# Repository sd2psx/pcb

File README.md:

# sd2psx: PCB

<table>
<tr>
    <td></td>
    <td></td>
    <td></td>
</tr>
</table>

## Production notes

The PCB must be produced in 0.8mm thickness. Production files are provided under the "Releases" tab. These do not include the through-hole OLED module.

## PSRAM notes (LY68L6400SLIT)

As of June 2023, the LY68L6400SLIT is no longer available from JLCPCB. I've also seen multiple reports of people receiving a **fake chip** when purchasing one from aliexpress. The following chips are a drop-in replacement for the PSRAM:

* IPUS IPS6404LSQ
* ESP PSRAM64H
* AP 6404L-3SQR - Available from [Mouser](https://www.mouser.com/ProductDetail/AP-Memory/APS6404L-3SQR-SN?qs=IS%252B4QmGtzzqsn3S5xo%2FEEg%3D%3D)
* Lyontek LY68L6400S

I recommend switching to the AP 6404L-3SQR module; it can be assembled by JLCPCB by first ordering it into your [personal parts library](https://jlcpcb.com/user-center/smtPrivateLibrary/?index=1).

## OLED module notes

The case requires a slim OLED module. The more common full-sized module will not fit into the case:

Examples of compatible modules:
- https://detail.tmall.com/item.htm?id=534583545403&skuId=3942158349315
- https://www.aliexpress.com/item/32638662748.html (make sure to select the smaller module marked as "New-White")

Spec sheet of a compatible module:

**Make sure that the pinout goes GND/VCC/SCL/SDA**. There are modules that swap GND/VCC around, these won't work.

## Assembly tips

When attaching the module to the PCB, remove protective OLED screen film (to prevent misalignment), then drop the module into the case so that the screen ends up flush against the case wall. Solder it on in that setup, then clip the pins:

There may be extra space between the pin header and the PCB, depending on your 3d print tolerances, but when fully assembled it should look nice and flush.

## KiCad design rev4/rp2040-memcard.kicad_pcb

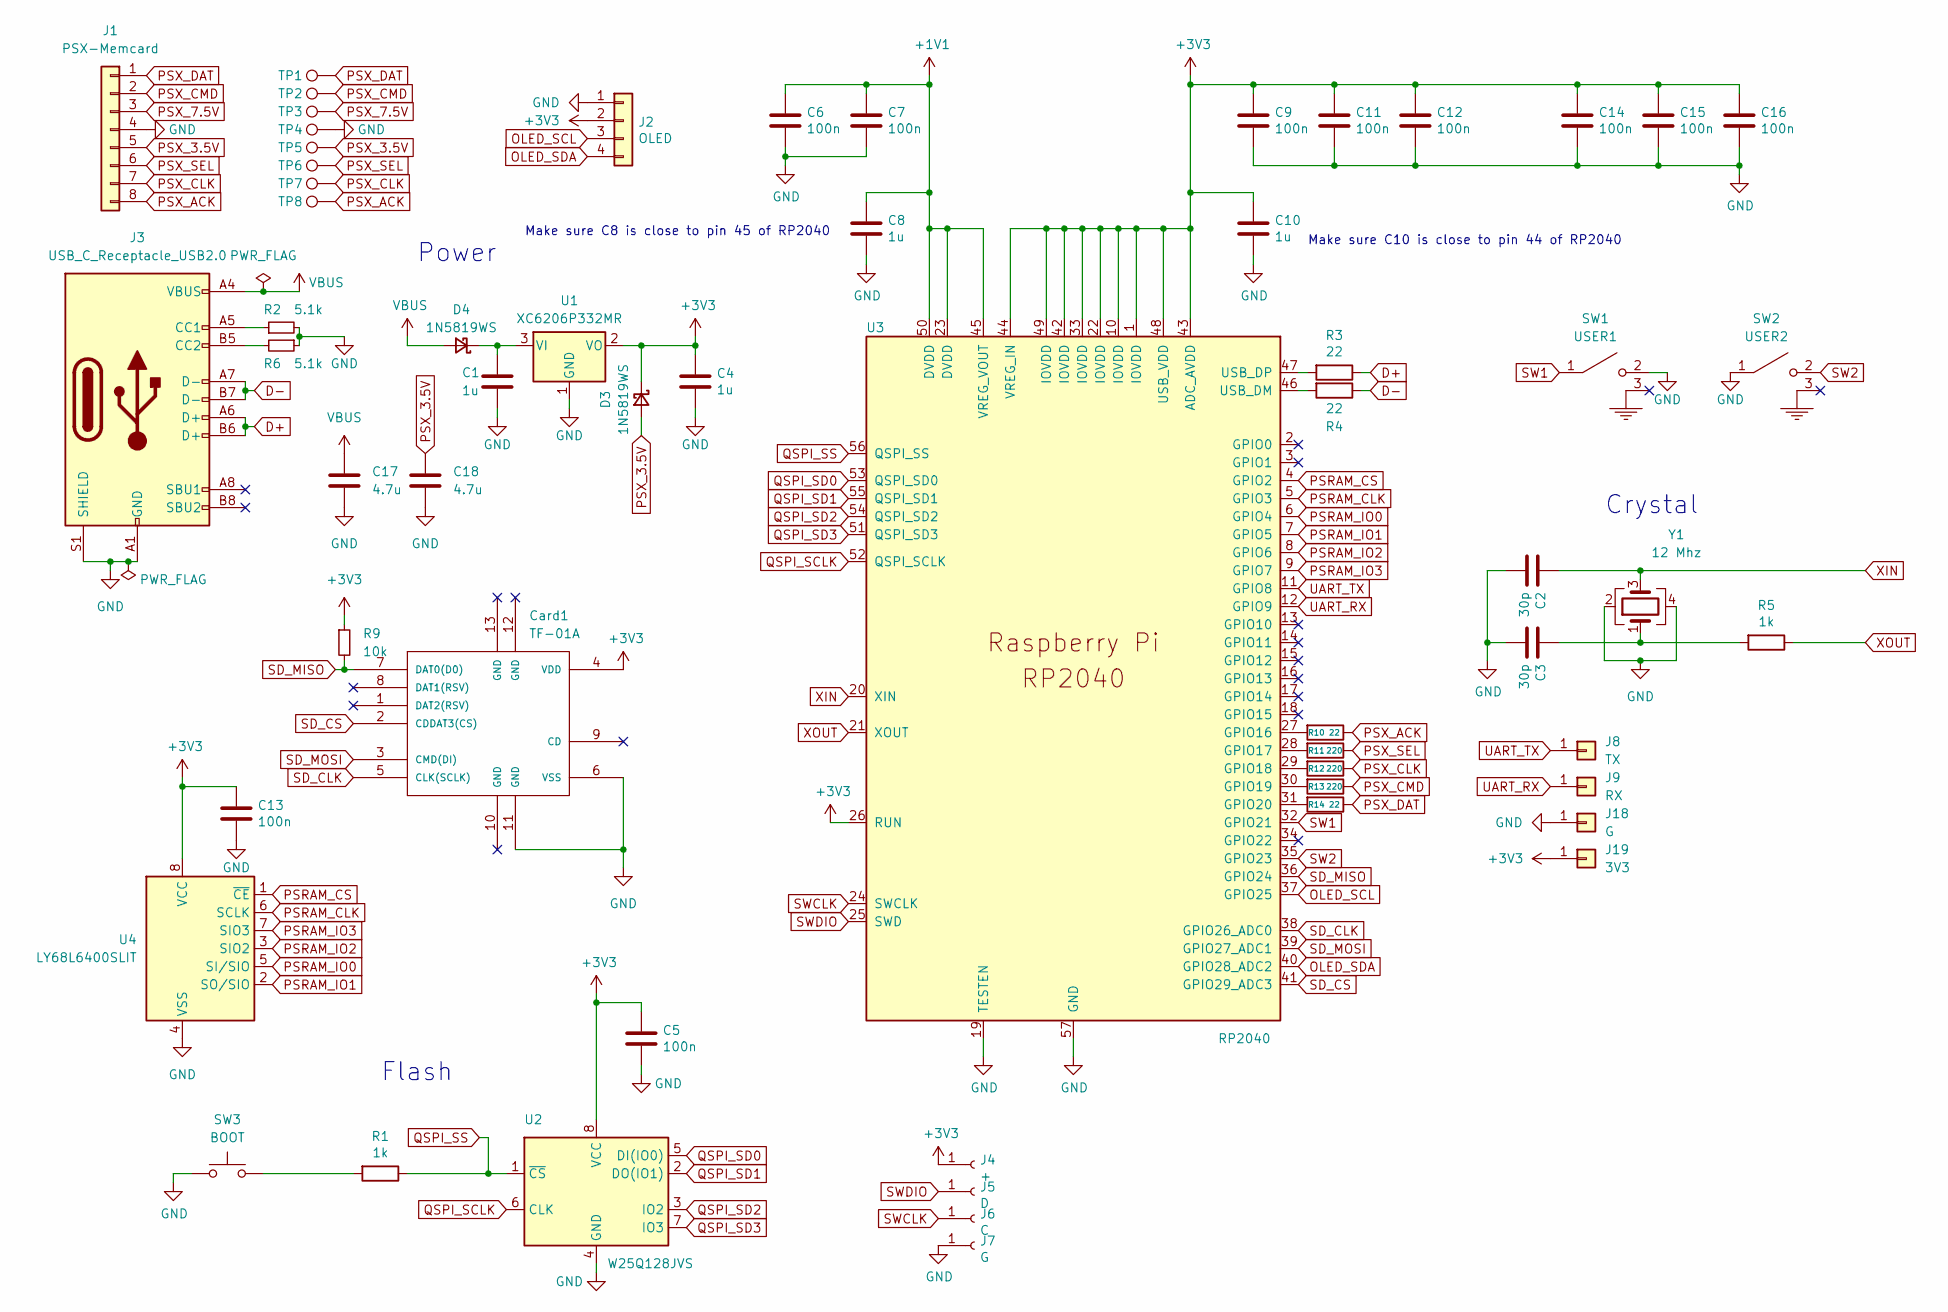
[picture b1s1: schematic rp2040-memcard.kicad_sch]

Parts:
C1, C4, C8, C10: 1u; C_0402_1005Metric; LCSC C52923
C2, C3: 30p; C_0402_1005Metric; LCSC C1570
C5, C6, C7, C9, C11, C12, C13, C14, C15, C16: 100n; C_0402_1005Metric; LCSC C1525
C17, C18: 4.7u; C_0402_1005Metric; LCSC C23733
Card1: TF-01A; TF-SMD_TF-01A; LCSC C91145
D3, D4: 1N5819WS; D_SOD-323; LCSC C191023
J1: PSX-Memcard; PlayStation_Memory_Card
J2: OLED; SSD1306
J3: USB_C_Receptacle_USB2.0; USB_C_Receptacle_HRO_TYPE-C-31-M-12; LCSC C2765186
J4: +; TestPoint_Pad_D1.5mm
J5: D; TestPoint_Pad_D1.5mm
J6: C; TestPoint_Pad_D1.5mm
J7: G; TestPoint_Pad_D1.5mm
J8: TX; TestPoint_Pad_D1.0mm
J9: RX; TestPoint_Pad_D1.0mm
J18: G; TestPoint_Pad_D1.0mm
J19: 3V3; TestPoint_Pad_D1.0mm
R1, R5: 1k; R_0402_1005Metric; LCSC C11702
R2, R6: 5.1k; R_0402_1005Metric; LCSC C25905
R3, R4, R10, R14: 22; R_0402_1005Metric; LCSC C25092
R9: 10k; R_0402_1005Metric; LCSC C25744
R11, R12, R13: 220; R_0402_1005Metric; LCSC C25091
SW1: USER1; SW-TH_TSC017A10026A
SW2: USER2; SW-TH_TSC017A10026A
SW3: BOOT; PinHeader_1x02_P2.00mm_Vertical; LCSC C393942
TP1, TP2, TP3, TP4, TP5, TP6, TP7, TP8: TestPoint; TestPoint_Pad_D1.0mm
U1: XC6206P332MR; SOT-23; LCSC C5446
U2: W25Q128JVS; SOIC-8_5.23x5.23mm_P1.27mm; LCSC C97521
U3: RP2040; RP2040-QFN-56; LCSC C2040
U4: LY68L6400SLIT; SOIC-8_3.9x4.9mm_P1.27mm; LCSC C261881
Y1: 12 Mhz; Crystal_SMD_3225-4Pin_3.2x2.5mm; LCSC C9002

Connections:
+1V1: C6.1, C7.1, C8.1, U3.23 (DVDD), U3.45 (VREG_VOUT), U3.50 (DVDD)
+3V3: C4.1, C5.1, C9.1, C10.1, C11.1, C12.1, C13.1, C14.1, C15.1, C16.1, Card1.4 (VDD), D3.1 (K), J2.2, J4.1, J19.1, R9.1, U1.2 (VO), U2.8 (VCC), U3.1 (IOVDD), U3.10 (IOVDD), U3.22 (IOVDD), U3.26 (RUN), U3.33 (IOVDD), U3.42 (IOVDD), U3.43 (ADC_AVDD), U3.44 (VREG_IN), U3.48 (USB_VDD), U3.49 (IOVDD), U4.8 (VCC)
D+: J3.A6 (D+), J3.B6 (D+), R3.1
D-: J3.A7 (D-), J3.B7 (D-), R4.1
GND: C1.2, C2.2, C3.2, C4.2, C5.2, C6.2, C7.2, C8.2, C9.2, C10.2, C11.2, C12.2, C13.2, C14.2, C15.2, C16.2, C17.1, C18.1, Card1.6 (VSS), Card1.11 (GND), J1.4, J2.1, J3.A1 (GND), J3.A12 (GND), J3.B1 (GND), J3.B12 (GND), J3.S1 (SHIELD), J7.1, J18.1, R2.2, R6.1, SW1.2, SW2.1, SW3.1, TP4.1, U1.1 (GND), U2.4 (GND), U3.19 (TESTEN), U3.57 (GND), U4.4 (VSS), Y1.2, Y1.4
unnamed: C1.1, D4.1 (K), U1.3 (VI)
unnamed: C3.1, R5.2, Y1.1
unnamed: J3.A5 (CC1), R2.1
unnamed: J3.B5 (CC2), R6.2
unnamed: R1.2, SW3.2
unnamed: R3.2, U3.47 (USB_DP)
unnamed: R4.2, U3.46 (USB_DM)
unnamed: R10.2, U3.27 (GPIO16)
unnamed: R11.2, U3.28 (GPIO17)
unnamed: R12.2, U3.29 (GPIO18)
unnamed: R13.2, U3.30 (GPIO19)
unnamed: R14.2, U3.31 (GPIO20)
OLED_SCL: J2.3, U3.37 (GPIO25)
OLED_SDA: J2.4, U3.40 (GPIO28_ADC2)
PSRAM_CLK: U3.5 (GPIO3), U4.6 (SCLK)
PSRAM_CS: U3.4 (GPIO2), U4.1 (~CE)
PSRAM_IO0: U3.6 (GPIO4), U4.5 (SI/SIO)
PSRAM_IO1: U3.7 (GPIO5), U4.2 (SO/SIO)
PSRAM_IO2: U3.8 (GPIO6), U4.3 (SIO2)
PSRAM_IO3: U3.9 (GPIO7), U4.7 (SIO3)
PSX_3.5V: C18.2, D3.2 (A), J1.5, TP5.1
PSX_7.5V: J1.3, TP3.1
PSX_ACK: J1.8, R10.1, TP8.1
PSX_CLK: J1.7, R12.1, TP7.1
PSX_CMD: J1.2, R13.1, TP2.1
PSX_DAT: J1.1, R14.1, TP1.1
PSX_SEL: J1.6, R11.1, TP6.1
QSPI_SCLK: U2.6 (CLK), U3.52 (QSPI_SCLK)
QSPI_SD0: U2.5 (DI(IO0)), U3.53 (QSPI_SD0)
QSPI_SD1: U2.2 (DO(IO1)), U3.55 (QSPI_SD1)
QSPI_SD2: U2.3 (IO2), U3.54 (QSPI_SD2)
QSPI_SD3: U2.7 (IO3), U3.51 (QSPI_SD3)
QSPI_SS: R1.1, U2.1 (~CS), U3.56 (QSPI_SS)
SD_CLK: Card1.5 (CLK(SCLK)), U3.38 (GPIO26_ADC0)
SD_CS: Card1.2 (CDDAT3(CS)), U3.41 (GPIO29_ADC3)
SD_MISO: Card1.7 (DAT0(D0)), R9.2, U3.36 (GPIO24)
SD_MOSI: Card1.3 (CMD(DI)), U3.39 (GPIO27_ADC1)
SW1: SW1.1, U3.32 (GPIO21)
SW2: SW2.2, U3.35 (GPIO23)
SWCLK: J6.1, U3.24 (SWCLK)
SWDIO: J5.1, U3.25 (SWD)
UART_RX: J9.1, U3.12 (GPIO9)
UART_TX: J8.1, U3.11 (GPIO8)
VBUS: C17.2, D4.2 (A), J3.A4 (VBUS), J3.A9 (VBUS), J3.B4 (VBUS), J3.B9 (VBUS)
XIN: C2.1, U3.20 (XIN), Y1.3
XOUT: R5.1, U3.21 (XOUT)

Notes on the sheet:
Make sure C10 is close to pin 44 of RP2040
Make sure C8 is close to pin 45 of RP2040
Crystal
Power
Flash

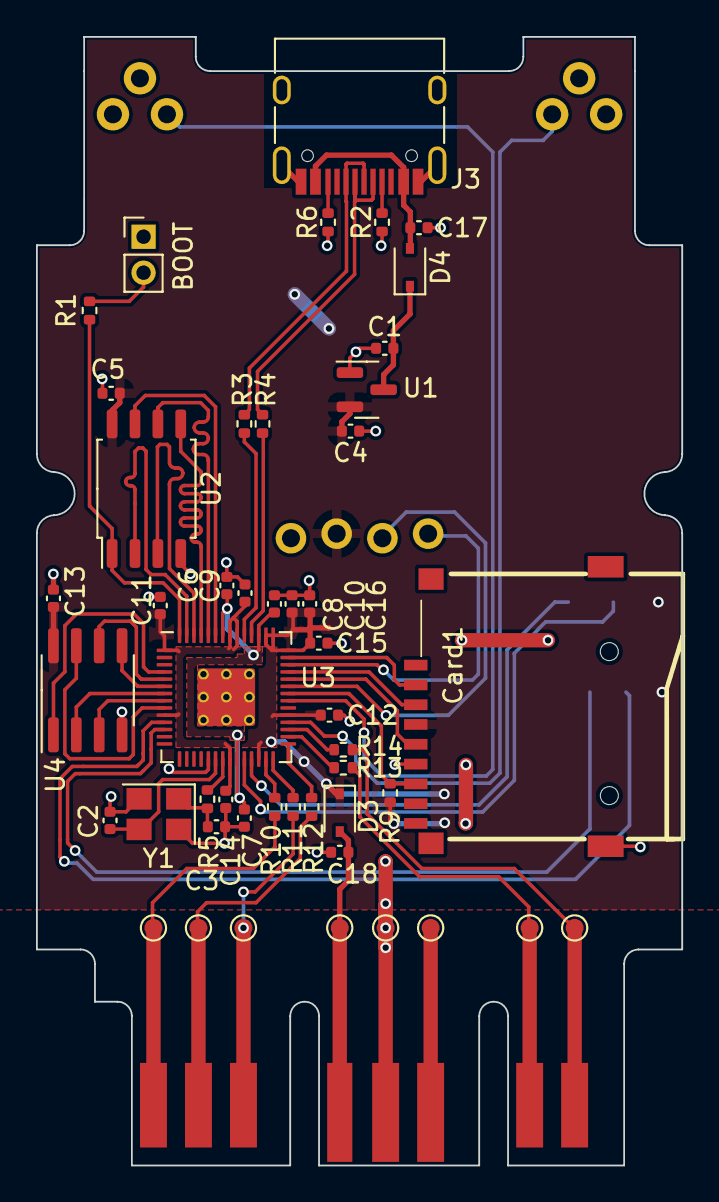
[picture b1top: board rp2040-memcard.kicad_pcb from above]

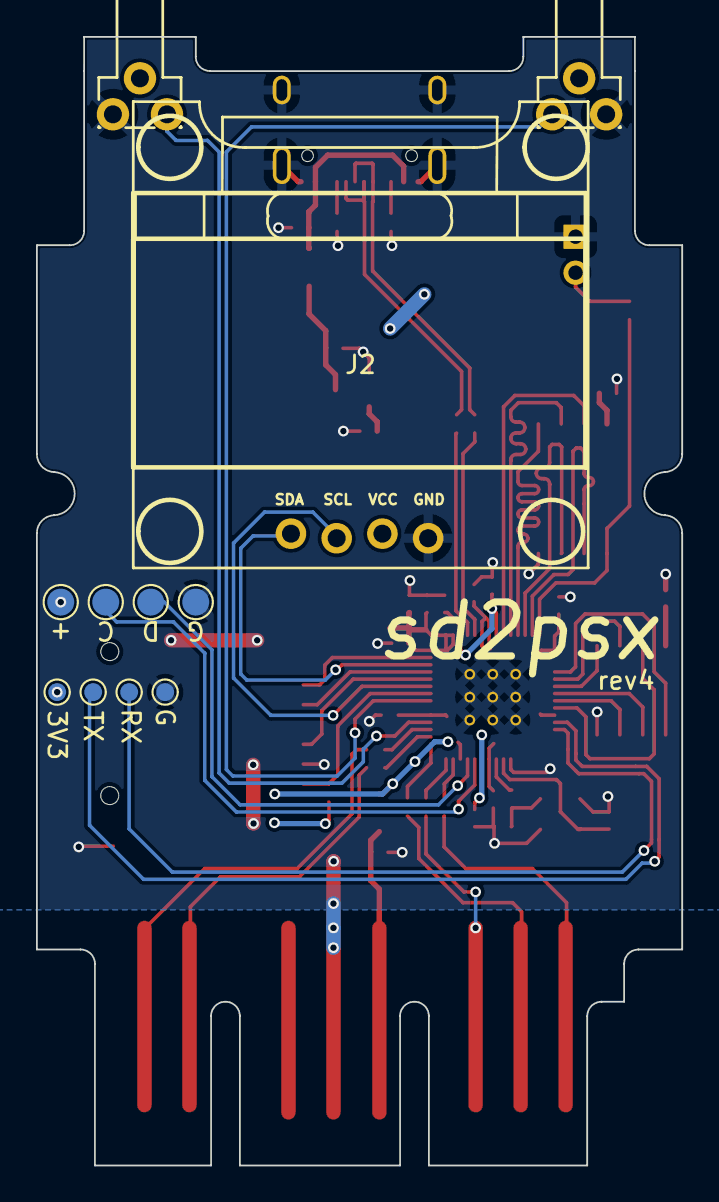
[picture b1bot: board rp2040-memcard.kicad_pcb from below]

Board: 2 copper layers, 35.9 x 62.7 mm, 60 parts (11 on the bottom side), 51 nets.

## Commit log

2022-10-05 initial
2022-10-05 add README
2023-02-26 move current pcb to rev3
2023-02-26 init rev4 as copy of rev3
2023-03-05 finalize rev4
2023-03-05 exclude drc errors for overlapping oled and switch
2023-03-06 remove boot button
2023-07-23 add psram notes
